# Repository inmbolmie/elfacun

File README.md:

# Elfacun Chess Interface Module

## News

__(2026/02/07): Elfacun software version R17 released with new Chessconnect mode :__ Link: ----- __[R17 files](https://github.com/inmbolmie/elfacun/releases/tag/R17)__ ----- Installation instructions: ----- __[Update Elfacun](./MANUAL.md#update-elfacun-software)__

## Elfacun chess module

This is an ongoing hardware project to create a chess module compatible with the old Mephisto modular boards (Exclusive, Modular, München) that will provide connectivity to a wide variety of chess apps and services.

The project currently comprises three devices:

* Elfacun chess module, that is the main module that enables the connectivity of modern apps to the Mephisto chess boards
* Brocoli power module, to be able to power Elfacun, the Mephisto board and some original modules from a regular USB power bank to get a true wireless chess board.
* Diablillo bridge adapter, that allows to connect wirelessly a physical Millennium chess module to Elfacun.

The hardware as well as software developed for it are published here under the GPL license.

To assist in the release of the module, I provide here links to some basic documentation:

* [V1 and V2 modules description and features](./DESCRIPTION.md)
* [Brocoli power module](./BROCOLI.md)
* [Diablillo bridge adapter](./DIABLILLO.md)
* [Compatibility chart](./COMPATIBILITY.md)
* [Limitations and remarks](./LIMITATIONS.md)
* [Operation manual](./MANUAL.md)
* [Make your own module](./SOURCE.md)

## Old News

__(2025/06/15): Source code and design files for V2 module released: ----- [Make your own module](./SOURCE.md)__

__(2025/02/23): Elfacun software version R15 released with chess 960 support:__ Link: ----- __[R15 files](https://github.com/inmbolmie/elfacun/releases/tag/R15)__ ----- Installation instructions: ----- __[Update Elfacun](./MANUAL.md#update-elfacun-software)__

__(2025/02/23): Diablillo software version R15 released with bug fixes:__ Link: ----- __[R15 files](https://github.com/inmbolmie/elfacun/releases/tag/R15)__ ----- Installation instructions: ----- __[Update Diabillo](./DIABLILLO.md#update-diablillo-software)__

__(2024/05/26): Elfacun software version R14 released with bug fixes:__ Link: ----- __[R14 files](https://github.com/inmbolmie/elfacun/releases/tag/R14)__ ----- Installation instructions: ----- __[Update Elfacun](./MANUAL.md#update-elfacun-software)__

__(2024/01/19): Elfacun software version R12 released with improvements for Lichess mode:__ Link: ----- __[R12 files](https://github.com/inmbolmie/elfacun/releases/tag/R12)__ ----- Installation instructions: ----- __[Update Elfacun](./MANUAL.md#update-elfacun-software)__

__(2023/09/16): Elfacun software version R11 released with new Chessnut-compatible mode:__ Link: ----- __[R11 files](https://github.com/inmbolmie/elfacun/releases/tag/R11)__ ----- Installation instructions: ----- __[Update Elfacun](./MANUAL.md#update-elfacun-software)__

__(2023/07/13): Elfacun software version R10 released with bug fixes:__ Link: ----- __[R10 files](https://github.com/inmbolmie/elfacun/releases/tag/R10)__ ----- Installation instructions: ----- __[Update Elfacun](./MANUAL.md#update-elfacun-software)__

__(2023/06/12): Elfacun software version R9 released with bug fixes:__ Link: ----- __[R9 files](https://github.com/inmbolmie/elfacun/releases/tag/R9)__ ----- Installation instructions: ----- __[Update Elfacun](./MANUAL.md#update-elfacun-software)__

__(2023/06/07): Elfacun software version R8 released with support for the new _Diablillo_ device:__ Link: ----- __[R8 files](https://github.com/inmbolmie/elfacun/releases/tag/R8)__ ----- Installation instructions: ----- __[Update Elfacun](./MANUAL.md#update-elfacun-software)__

__(2023/03/05): Elfacun software version R7 released with on-screen LED indications in passive mode, board position storage and customizable sound and BLE power level:__ Link: ----- __[R7 files](https://github.com/inmbolmie/elfacun/releases/tag/R7)__ ----- Installation instructions: ----- __[Update Elfacun](./MANUAL.md#update-elfacun-software)__

__(2023/02/08): Elfacun software version R6 released with opponent ELO range on Lichess challenges:__ Link: ----- __[R6 files](https://github.com/inmbolmie/elfacun/releases/tag/R6)__ ----- Installation instructions: ----- __[Update Elfacun](./MANUAL.md#update-elfacun-software)__

__(2023/01/30): Elfacun software version R5 released with some bug fixes:__ Link: ----- __[R5 files](https://github.com/inmbolmie/elfacun/releases/tag/R5)__ ----- Installation instructions: ----- __[Update Elfacun](./MANUAL.md#update-elfacun-software)__

__(2023/01/28): Elfacun hardware version 2 released with new features and improved compatibility with original modules:__ Links: ----- __[V2 features](./DESCRIPTION.md#features)__ ----- __[V2 manual](./MANUAL.md#new-v1-and-v2-features)__ ----- __[V2 compatibility](./COMPATIBILITY.md#v2-with-original-mephisto-modules)__

__(2023/01/28): Brocoli battery power module for Elfacun:__ Link: ----- __[Brocoli power module](./BROCOLI.md)__

__(2022/05/04): Elfacun software version R4 released with some bug fixes: [R4 files](https://github.com/inmbolmie/elfacun/releases/tag/R4)__ Installation instructions: ----- __[Update Elfacun](./MANUAL.md#update-elfacun-software)__

__(2022/09/03): Source code and design files released: ----- [Make your own module](./SOURCE.md)__

_"DGT", "Millennium", "Mephisto", "Chessnut" and "IChessOne" are trademarks of their respective owners.
All the trademarks are used nominatively to indicate compatibility, and do not indicate affiliation to or endorsement by the trademark owners._

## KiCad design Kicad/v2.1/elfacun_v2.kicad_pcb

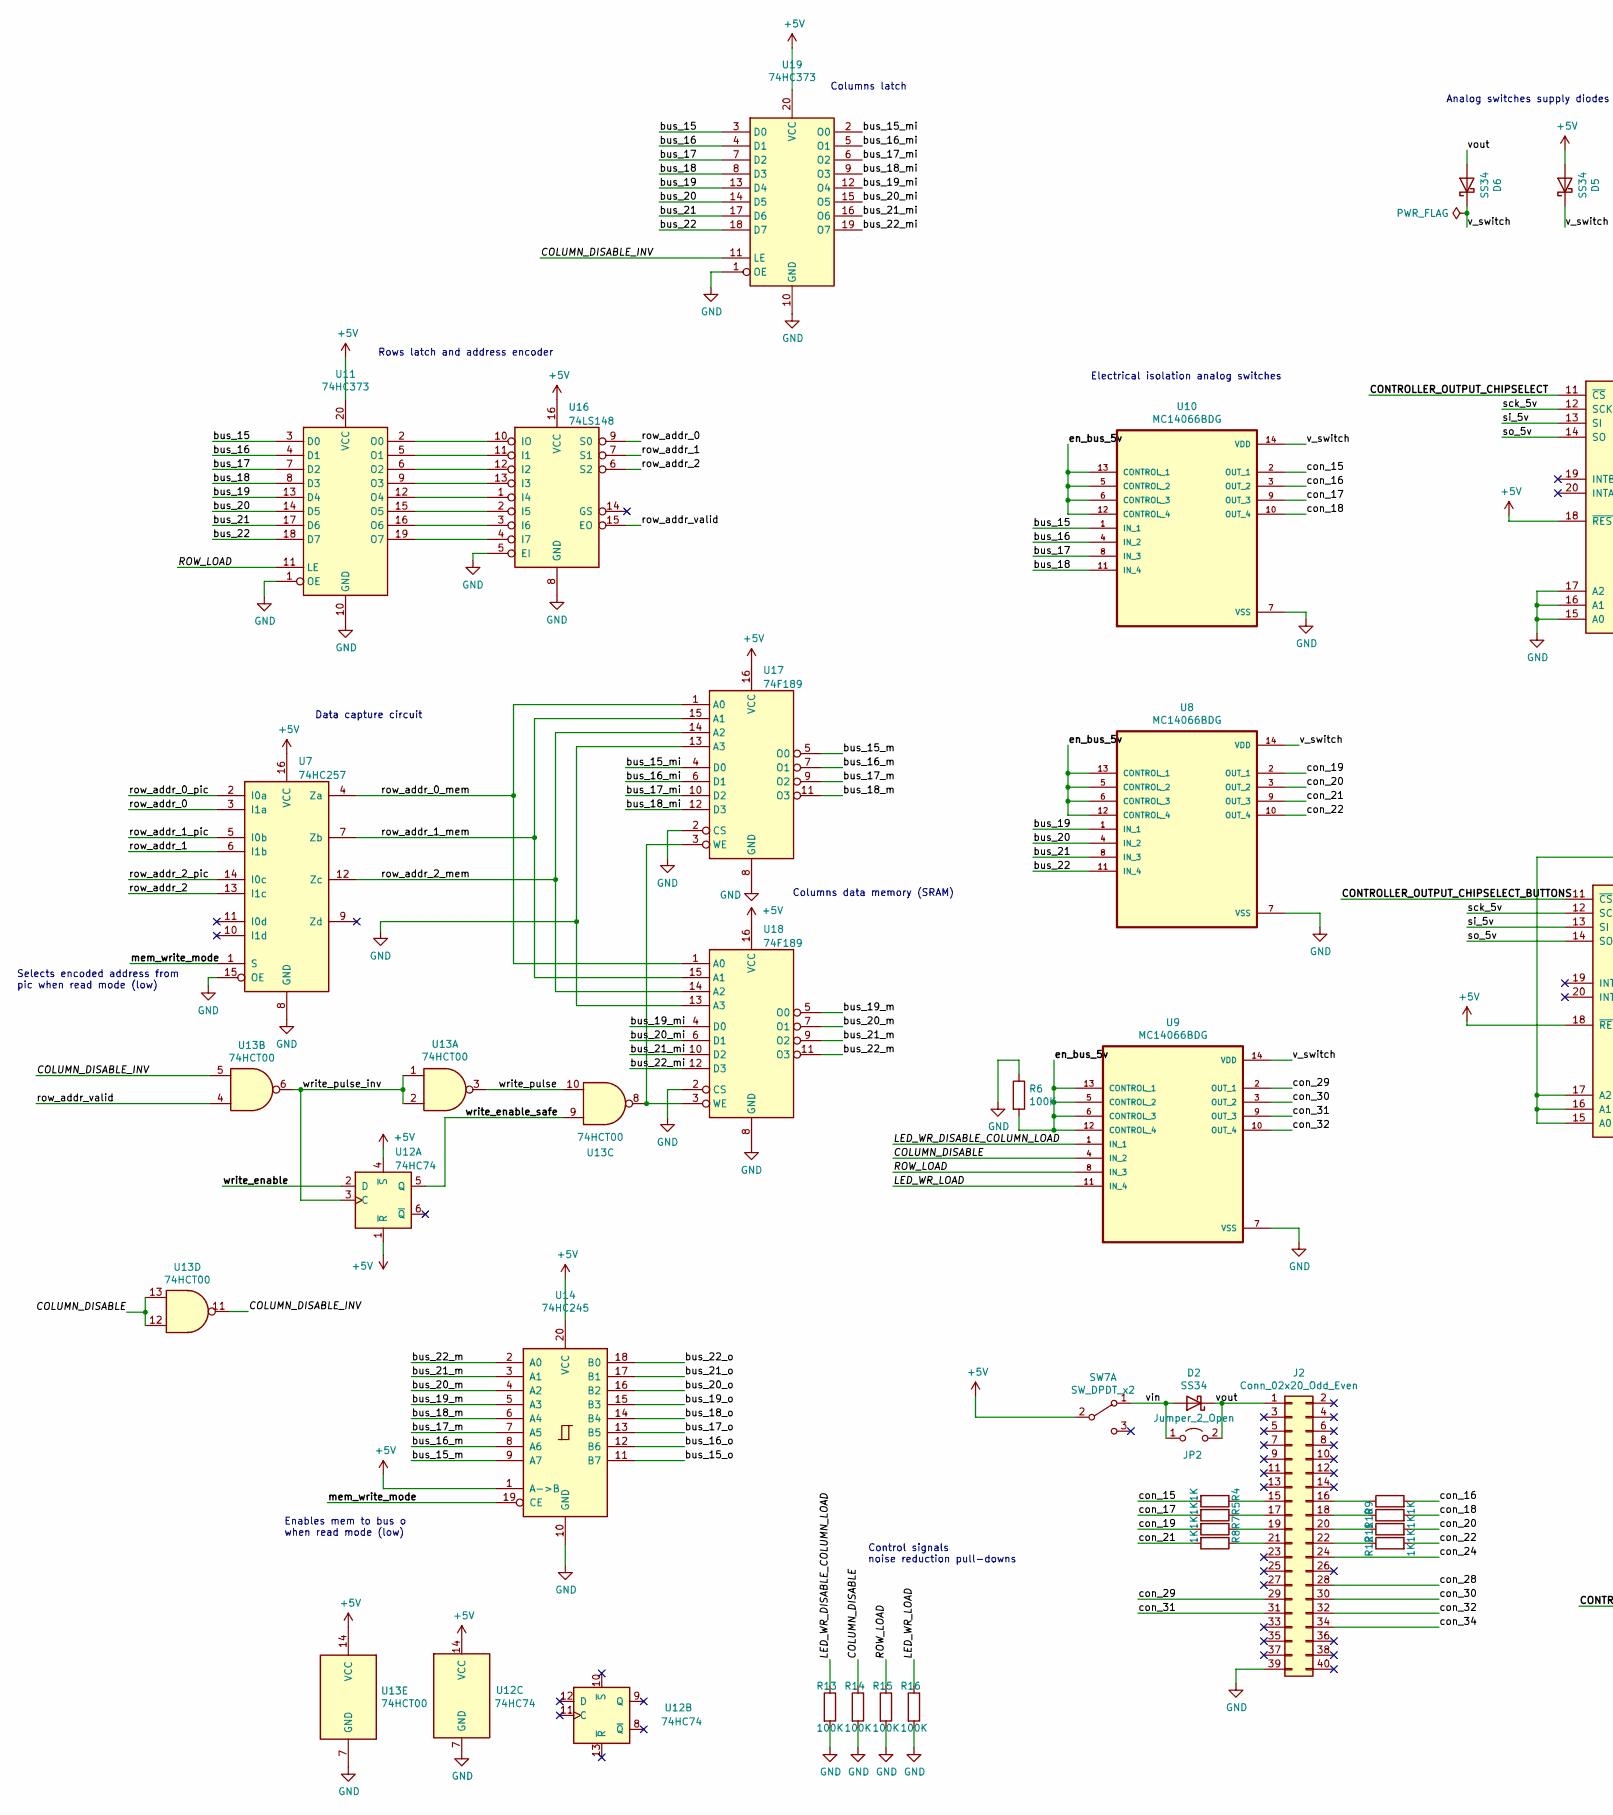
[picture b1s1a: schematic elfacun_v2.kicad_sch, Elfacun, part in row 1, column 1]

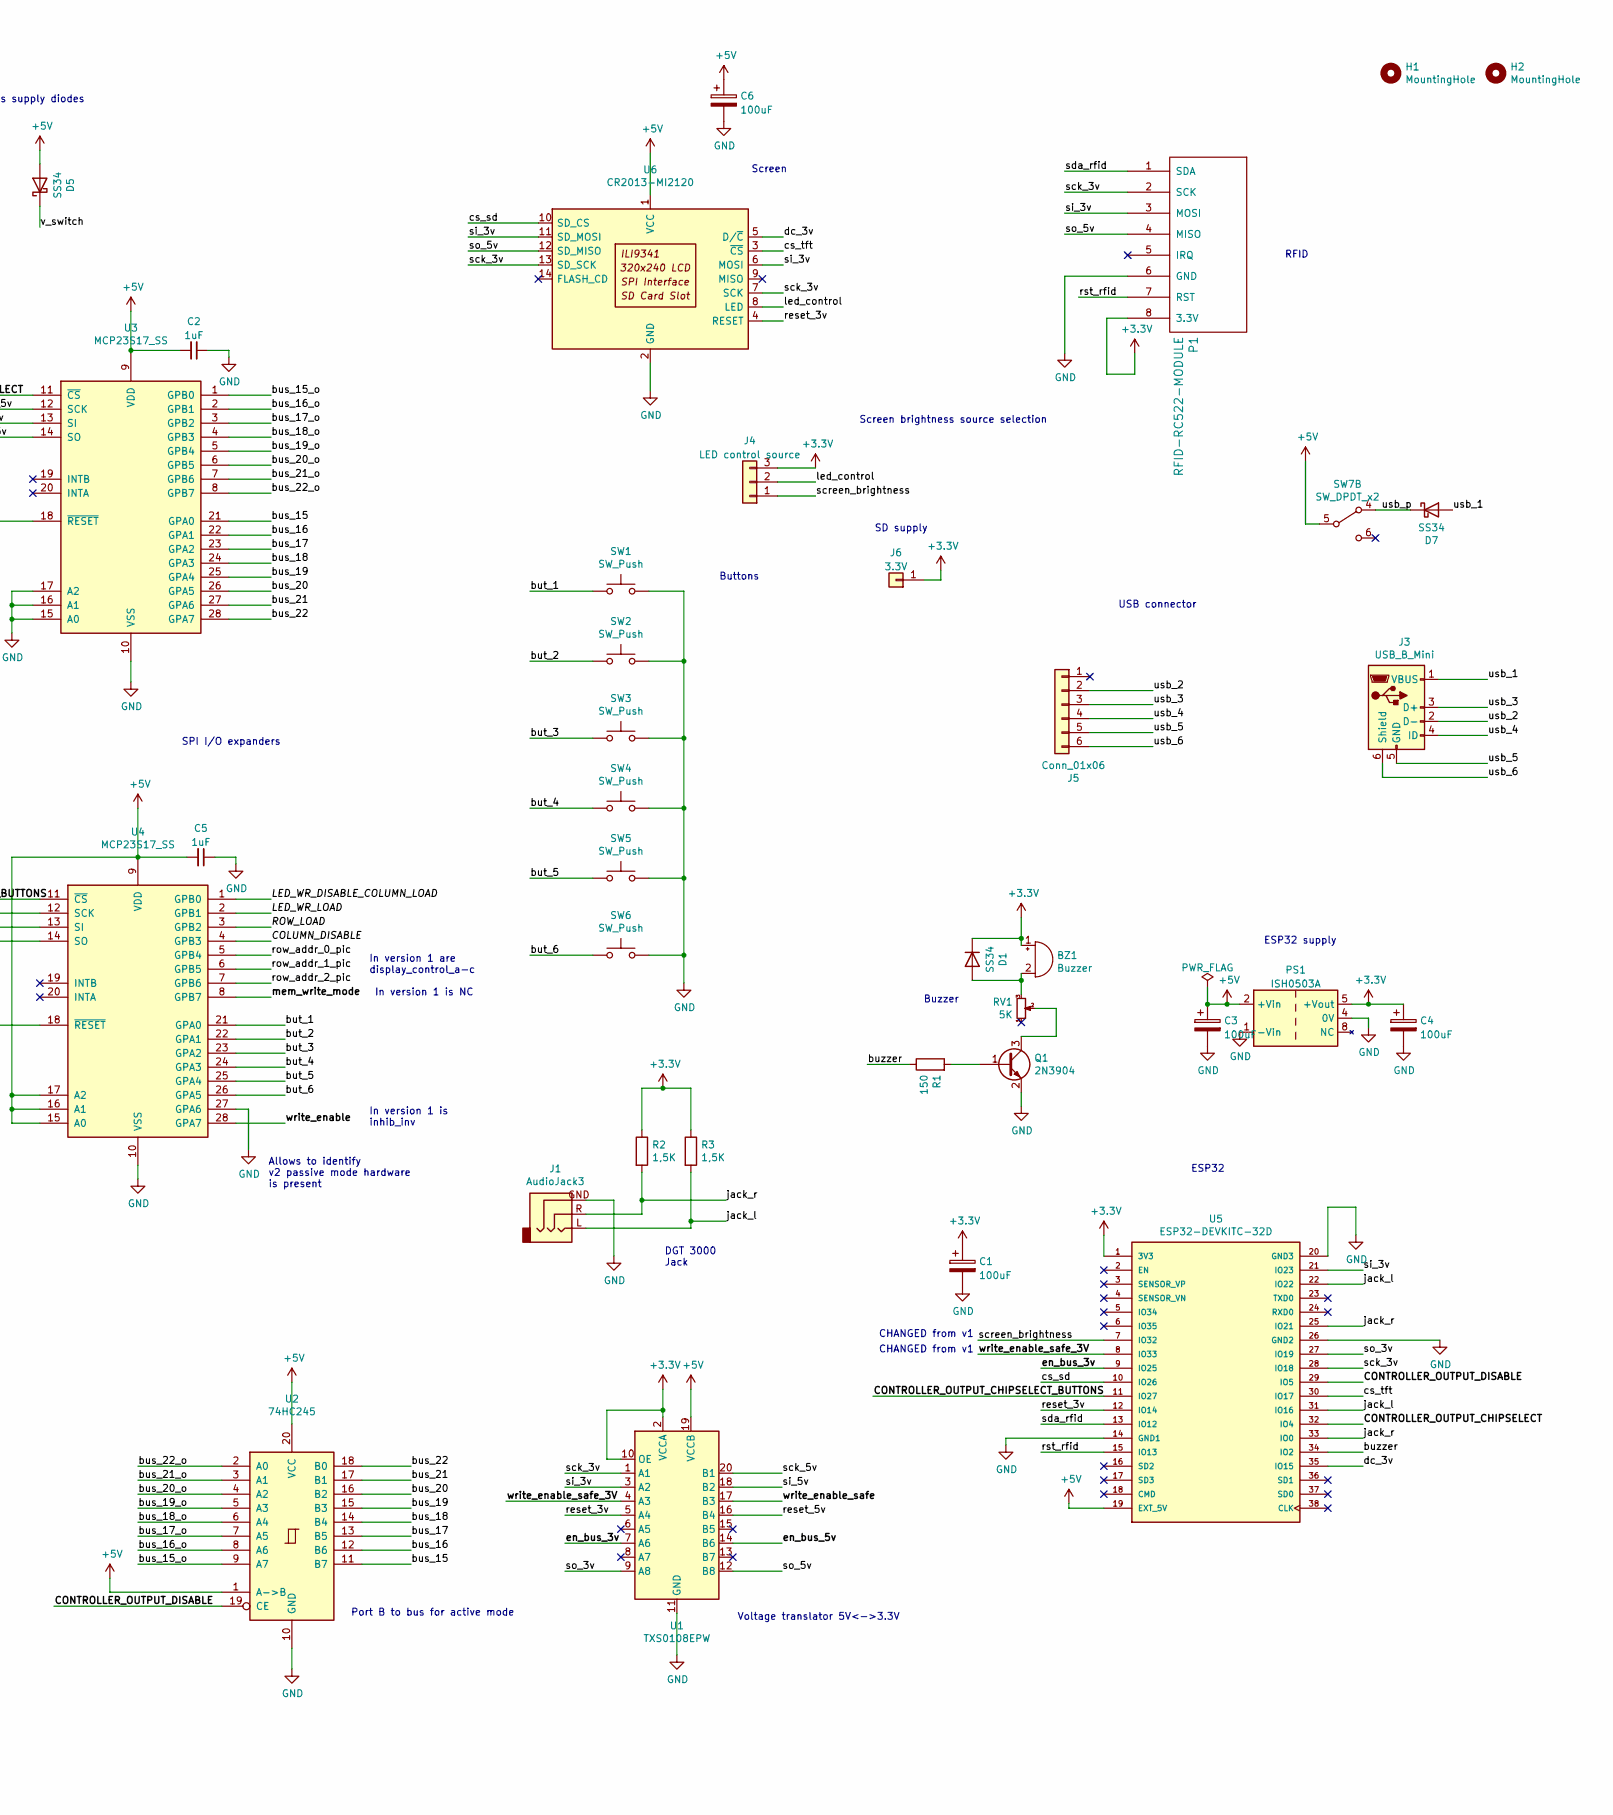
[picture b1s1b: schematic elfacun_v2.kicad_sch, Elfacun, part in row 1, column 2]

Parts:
BZ1: Buzzer; MagneticBuzzer_ProSignal_ABT-410-RC
C1, C3, C4, C6: 100uF; C_1206_3216Metric; LCSC C15008
C2, C5: 1uF; C_0603_1608Metric; LCSC C15849
D1, D2, D5, D6, D7: SS34; D_SMA; LCSC C8678
H1, H2: MountingHole; MountingHole_3.5mm
J1: AudioJack3; AUDIO-TH_PJ-3059-X; LCSC C319114
J2: Conn_02x20_Odd_Even; PinHeader_2x20_P2.54mm_Horizontal
J3: USB_B_Mini; USB_Mini-B_Tensility_54-00023_Vertical; LCSC C13453
J4: LED control source; PinHeader_1x03_P2.54mm_Vertical
J5: Conn_01x06; PinHeader_1x06_P2.54mm_Horizontal
J6: 3.3V; PinHeader_1x01_P2.54mm_Horizontal
JP2: Jumper_2_Open; PinHeader_1x02_P2.54mm_Vertical
P1: RFID-RC522-MODULE; PinHeader_1x08_P2.54mm_Vertical
PS1: ISH0503A; ISE0303A
Q1: 2N3904; SOT-23; LCSC C18536
R1: 150; R_0603_1608Metric; LCSC C22808
R2, R3: 1,5K; R_0603_1608Metric; LCSC C22843
R4, R5, R7, R8, R9, R10, R11, R12: 1K; R_0603_1608Metric; LCSC C21190
R6, R13, R14, R15, R16: 100K; R_0603_1608Metric; LCSC C25803
RV1: 5K; RES-ADJ-SMD_G32AT; LCSC C128119
SW1, SW2, SW3, SW4, SW5, SW6: SW_Push; honyone_pb13_switch
SW7: SW_DPDT_x2; SW-TH_K3-2235S-K1
U1: TXS0108EPW; TSSOP-20_4.4x6.5mm_P0.65mm; LCSC C53406
U2, U14: 74HC245; SO-20_5.3x12.6mm_P1.27mm; LCSC C133641
U3, U4: MCP23S17_SS; DIP-28_W7.62mm; LCSC C145413
U5: ESP32-DEVKITC-32D; MODULE_ESP32-DEVKITC-32D
U6: CR2013-MI2120
U7: 74HC257; SOIC-16_3.9x9.9mm_P1.27mm; LCSC C7645
U8, U9, U10: MC14066BDG; SOIC-14_3.9x8.7mm_P1.27mm; LCSC C52828
U11, U19: 74HC373; TSSOP-20_4.4x6.5mm_P0.65mm; LCSC C132998
U12: 74HC74; SO-14_3.9x8.65mm_P1.27mm; LCSC C39990
U13: 74HCT00; SOIC-14_3.9x8.7mm_P1.27mm
U16: 74LS148; SOP-16_3.9x9.9mm_P1.27mm; LCSC C521196
U17, U18: 74F189; DIP-16_W7.62mm

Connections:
+3V3: BZ1.1 (-), C1.1, C4.1, D1.1 (K), J4.3, J6.1, P1.8 (3.3V), PS1.5 (+Vout), R2.1, R3.1, U1.2 (VCCA), U1.10 (OE), U5.1 (3V3)
+5V: C2.2, C3.1, C5.2, C6.1, D5.2 (A), PS1.2 (+Vin), SW7.2 (B), SW7.5 (B), U1.19 (VCCB), U2.1 (A->B), U2.20 (VCC), U3.9 (VDD), U3.18 (~RESET), U4.9 (VDD), U4.15 (A0), U4.16 (A1), U4.17 (A2), U4.18 (~RESET), U5.19 (EXT_5V), U6.1 (VCC), U7.16 (VCC), U11.20 (VCC), U12.1 (~R), U12.4 (~S), U12.14 (VCC), U13.14 (VCC), U14.1 (A->B), U14.20 (VCC), U16.16 (VCC), U17.16 (VCC), U18.16 (VCC), U19.20 (VCC)
/COLUMN_DISABLE: R14.1, U4.4 (GPB3), U9.4 (IN_2), U13.12, U13.13
/COLUMN_DISABLE_INV: U13.5, U13.11, U19.11 (LE)
/CONTROLLER_OUTPUT_CHIPSELECT: U3.11 (~CS), U5.32 (IO4)
/CONTROLLER_OUTPUT_CHIPSELECT_BUTTONS: U4.11 (~CS), U5.11 (IO27)
/CONTROLLER_OUTPUT_DISABLE: U2.19 (CE), U5.29 (IO5)
/LED_WR_DISABLE_COLUMN_LOAD: R13.1, U4.1 (GPB0), U9.1 (IN_1)
/LED_WR_LOAD: R16.1, U4.2 (GPB1), U9.11 (IN_4)
/ROW_LOAD: R15.1, U4.3 (GPB2), U9.8 (IN_3), U11.11 (LE)
/bus_15: U2.11 (B7), U3.21 (GPA0), U10.1 (IN_1), U11.3 (D0), U19.3 (D0)
/bus_15_m: U14.9 (A7), U17.5 (O0)
/bus_15_mi: U17.4 (D0), U19.2 (O0)
/bus_15_o: U2.9 (A7), U3.1 (GPB0), U14.11 (B7)
/bus_16: U2.12 (B6), U3.22 (GPA1), U10.4 (IN_2), U11.4 (D1), U19.4 (D1)
/bus_16_m: U14.8 (A6), U17.7 (O1)
/bus_16_mi: U17.6 (D1), U19.5 (O1)
/bus_16_o: U2.8 (A6), U3.2 (GPB1), U14.12 (B6)
/bus_17: U2.13 (B5), U3.23 (GPA2), U10.8 (IN_3), U11.7 (D2), U19.7 (D2)
/bus_17_m: U14.7 (A5), U17.9 (O2)
/bus_17_mi: U17.10 (D2), U19.6 (O2)
/bus_17_o: U2.7 (A5), U3.3 (GPB2), U14.13 (B5)
/bus_18: U2.14 (B4), U3.24 (GPA3), U10.11 (IN_4), U11.8 (D3), U19.8 (D3)
/bus_18_m: U14.6 (A4), U17.11 (O3)
/bus_18_mi: U17.12 (D3), U19.9 (O3)
/bus_18_o: U2.6 (A4), U3.4 (GPB3), U14.14 (B4)
/bus_19: U2.15 (B3), U3.25 (GPA4), U8.1 (IN_1), U11.13 (D4), U19.13 (D4)
/bus_19_m: U14.5 (A3), U18.5 (O0)
/bus_19_mi: U18.4 (D0), U19.12 (O4)
/bus_19_o: U2.5 (A3), U3.5 (GPB4), U14.15 (B3)
/bus_20: U2.16 (B2), U3.26 (GPA5), U8.4 (IN_2), U11.14 (D5), U19.14 (D5)
/bus_20_m: U14.4 (A2), U18.7 (O1)
/bus_20_mi: U18.6 (D1), U19.15 (O5)
/bus_20_o: U2.4 (A2), U3.6 (GPB5), U14.16 (B2)
/bus_21: U2.17 (B1), U3.27 (GPA6), U8.8 (IN_3), U11.17 (D6), U19.17 (D6)
/bus_21_m: U14.3 (A1), U18.9 (O2)
/bus_21_mi: U18.10 (D2), U19.16 (O6)
/bus_21_o: U2.3 (A1), U3.7 (GPB6), U14.17 (B1)
/bus_22: U2.18 (B0), U3.28 (GPA7), U8.11 (IN_4), U11.18 (D7), U19.18 (D7)
/bus_22_m: U14.2 (A0), U18.11 (O3)
/bus_22_mi: U18.12 (D3), U19.19 (O7)
/bus_22_o: U2.2 (A0), U3.8 (GPB7), U14.18 (B0)
/but_1: SW1.1, U4.21 (GPA0)
/but_2: SW2.1, U4.22 (GPA1)
/but_3: SW3.1, U4.23 (GPA2)
/but_4: SW4.1, U4.24 (GPA3)
/but_5: SW5.1, U4.25 (GPA4)
/but_6: SW6.1, U4.26 (GPA5)
/buzzer: R1.1, U5.34 (IO2)
/con_15: R4.2, U10.2 (OUT_1)
/con_16: R9.2, U10.3 (OUT_2)
/con_17: R5.2, U10.9 (OUT_3)
/con_18: R10.2, U10.10 (OUT_4)
/con_19: R7.2, U8.2 (OUT_1)
/con_20: R11.2, U8.3 (OUT_2)
/con_21: R8.2, U8.9 (OUT_3)
/con_22: R12.2, U8.10 (OUT_4)
/con_24: J2.24
/con_28: J2.28
/con_29: J2.29, U9.2 (OUT_1)
/con_30: J2.30, U9.3 (OUT_2)
/con_31: J2.31, U9.9 (OUT_3)
/con_32: J2.32, U9.10 (OUT_4)
/con_34: J2.34
/cs_sd: U5.10 (IO26), U6.10 (SD_CS)
/cs_tft: U5.30 (IO17), U6.3 (~CS)
/dc_3v: U5.35 (IO15), U6.5 (D/~C)
/en_bus_3v: U1.7 (A6), U5.9 (IO25)
/en_bus_5v: R6.2, U1.14 (B6), U8.5 (CONTROL_2), U8.6 (CONTROL_3), U8.12 (CONTROL_4), U8.13 (CONTROL_1), U9.5 (CONTROL_2), U9.6 (CONTROL_3), U9.12 (CONTROL_4), U9.13 (CONTROL_1), U10.5 (CONTROL_2), U10.6 (CONTROL_3), U10.12 (CONTROL_4), U10.13 (CONTROL_1)
/jack_l: J1.L, R3.2, U5.22 (IO22), U5.31 (IO16)
/jack_r: J1.R, R2.2, U5.25 (IO21), U5.33 (IO0)
/led_control: J4.2, U6.8 (LED)
/mem_write_mode: U4.8 (GPB7), U7.1 (S), U14.19 (CE)
/reset_3v: U1.5 (A4), U5.12 (IO14), U6.4 (RESET)
/reset_5v: U1.16 (B4)
/row_addr_0: U7.3 (I1a), U16.9 (S0)
/row_addr_0_mem: U7.4 (Za), U17.1 (A0), U18.1 (A0)
/row_addr_0_pic: U4.5 (GPB4), U7.2 (I0a)
/row_addr_1: U7.6 (I1b), U16.7 (S1)
/row_addr_1_mem: U7.7 (Zb), U17.15 (A1), U18.15 (A1)
/row_addr_1_pic: U4.6 (GPB5), U7.5 (I0b)
/row_addr_2: U7.13 (I1c), U16.6 (S2)
/row_addr_2_mem: U7.12 (Zc), U17.14 (A2), U18.14 (A2)
/row_addr_2_pic: U4.7 (GPB6), U7.14 (I0c)
/row_addr_valid: U13.4, U16.15 (EO)
/rst_rfid: P1.7 (RST), U5.15 (IO13)
/sck_3v: P1.2 (SCK), U1.1 (A1), U5.28 (IO18), U6.7 (SCK), U6.13 (SD_SCK)
/sck_5v: U1.20 (B1), U3.12 (SCK), U4.12 (SCK)
/screen_brightness: J4.1, U5.7 (IO32)
/sda_rfid: P1.1 (SDA), U5.13 (IO12)
/si_3v: P1.3 (MOSI), U1.3 (A2), U5.21 (IO23), U6.6 (MOSI), U6.11 (SD_MOSI)
/si_5v: U1.18 (B2), U3.13 (SI), U4.13 (SI)
/so_3v: U1.9 (A8), U5.27 (IO19)
/so_5v: P1.4 (MISO), U1.12 (B8), U3.14 (SO), U4.14 (SO), U6.12 (SD_MISO)
/usb_1: D7.2 (A), J3.1 (VBUS)
/usb_2: J3.2 (D-), J5.2
/usb_3: J3.3 (D+), J5.3
/usb_4: J3.4 (ID), J5.4
/usb_5: J3.5 (GND), J5.5
/usb_6: J3.6 (Shield), J5.6
/usb_p: D7.1 (K), SW7.4 (A)
/v_switch: D5.1 (K), D6.1 (K), U8.14 (VDD), U9.14 (VDD), U10.14 (VDD)
/vin: D2.2 (A), JP2.1 (A), SW7.1 (A)
/vout: D2.1 (K), D6.2 (A), J2.1, JP2.2 (B)
/write_enable: U4.28 (GPA7), U12.2 (D)
/write_enable_safe: U1.17 (B3), U12.5 (Q), U13.9
/write_enable_safe_3V: U1.4 (A3), U5.8 (IO33)
/write_pulse: U13.3, U13.10
/write_pulse_inv: U12.3 (C), U13.1, U13.2, U13.6
GND: C1.2, C2.1, C3.2, C4.2, C5.1, C6.2, J1.GND, J2.39, P1.6 (GND), PS1.1 (-Vin), PS1.4 (0V), Q1.2 (E), R6.1, R13.2, R14.2, R15.2, R16.2, SW1.2, SW2.2, SW3.2, SW4.2, SW5.2, SW6.2, U1.11 (GND), U2.10 (GND), U3.10 (VSS), U3.15 (A0), U3.16 (A1), U3.17 (A2), U4.10 (VSS), U4.27 (GPA6), U5.14 (GND1), U5.20 (GND3), U5.26 (GND2), U6.2 (GND), U7.8 (GND), U7.15 (OE), U8.7 (VSS), U9.7 (VSS), U10.7 (VSS), U11.1 (OE), U11.10 (GND), U12.7 (GND), U13.7 (GND), U14.10 (GND), U16.5 (EI), U16.8 (GND), U17.2 (CS), U17.8 (GND), U17.13 (A3), U18.2 (CS), U18.8 (GND), U18.13 (A3), U19.1 (OE), U19.10 (GND)
unnamed: BZ1.2 (+), D1.2 (A), RV1.3
unnamed: J2.15, R4.1
unnamed: J2.16, R9.1
unnamed: J2.17, R5.1
unnamed: J2.18, R10.1
unnamed: J2.19, R7.1
unnamed: J2.20, R11.1
unnamed: J2.21, R8.1
unnamed: J2.22, R12.1
unnamed: Q1.1 (B), R1.2
unnamed: Q1.3 (C), RV1.2
unnamed: U11.2 (O0), U16.10 (IO)
unnamed: U11.5 (O1), U16.11 (I1)
unnamed: U11.6 (O2), U16.12 (I2)
unnamed: U11.9 (O3), U16.13 (I3)
unnamed: U11.12 (O4), U16.1 (I4)
unnamed: U11.15 (O5), U16.2 (I5)
unnamed: U11.16 (O6), U16.3 (I6)
unnamed: U11.19 (O7), U16.4 (I7)
unnamed: U13.8, U17.3 (WE), U18.3 (WE)

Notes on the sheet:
Buzzer
Enables mem to bus o when read mode (low)
Selects encoded address from pic when read mode (low)
ESP32
Analog switches supply diodes
Screen brightness source selection
Port B to bus for active mode
Columns data memory (SRAM)
SD supply
USB connector
Buttons
CHANGED from v1
SPI I/O expanders
DGT 3000 Jack
RFID
Screen
In version 1 is NC
ESP32 supply
Rows latch and address encoder
Control signals noise reduction pull-downs
Electrical isolation analog switches
Data capture circuit
In version 1 is inhib_inv
Allows to identify v2 passive mode hardware is present
In version 1 are display_control_a-c
Voltage translator 5V<->3.3V
Columns latch

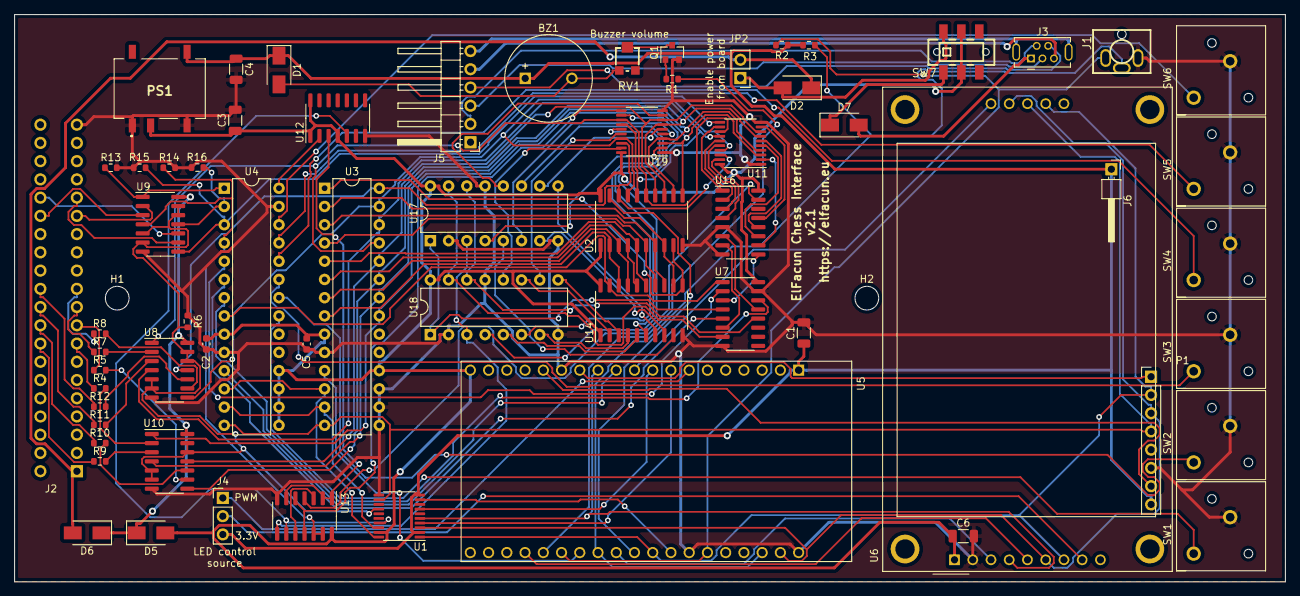
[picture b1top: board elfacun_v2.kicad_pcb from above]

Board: 2 copper layers, 177.0 x 79.0 mm, 66 parts (0 on the bottom side), 126 nets.

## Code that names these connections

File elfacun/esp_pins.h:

/*  
    ElFacun Chess Module software for ESP32
    © 2022 Inmbolmie inmbolmie [at] gmail [dot] com
    Distributed under the GNU GPL V3.0 license
    
    This program is distributed WITHOUT ANY WARRANTY, even the 
    implied warranty of MERCHANTABILITY or FITNESS FOR A PARTICULAR 
    PURPOSE.  See the GNU General Public License for more details.
*/

//ESP32 I/O PORTS ASSIGNMENTS
//00 Audio Jack R (I2C master)

//02 Buzzer
//04 CONTROLLER OUTPUT CS
//05 CONTROLLER OUTPUT DISABLE

//12 RFID CS
//13 RFID RESET
//14 SPI RESET 3V
//15 DISPLAY D/C 3V
//16 Audio Jack L (I2C master)
//17 DISPLAY CS
//18 SPI SCK 3V
//19 SPI SO 3V

//21 Audio Jack R (I2C slave)
//22 Audio Jack L (I2C slave)
//23 SPI SI 3V

//25 ENABLE BUS SWITCHES
//26 SD CARD CS
//27 CONTROLLER OUTPUT BUTTONS CS

//32 LATCH DISABLE B (columns)
//33 LATCH DISABLE A (rows)


//Board interface control pins

//RFID
#define RFID_CS 12

//SD INTERFACE
#define SD_CS 26

//ENABLE BUS SWITCHES
#define EN_BUS 25

//Data from controller to board
#define CONTROLLER_OUTPUT_DISABLE 5
#define CONTROLLER_OUTPUT_CHIPSELECT 4
#define CONTROLLER_OUTPUT_CHIPSELECT_BUTTONS 27


//Board latches controlled through 40-pin connector with the 23S17. So the numbers are 23S17 port numbers
//BUS_29
#define LED_WR_DISABLE_COLUMN_LOAD_EX 8
//BUS_32
#define LED_WR_LOAD_EX 9
//BUS_31
#define ROW_LOAD_EX 10
//BUS_30
#define COLUMN_DISABLE_EX 11
//DISPLAY CONTROL
#define DISPLAY_CTRL_A 12
#define DISPLAY_CTRL_B 13
#define DISPLAY_CTRL_C 14

//Special data latches for passive mode
#define LATCH_ROWS_DISABLE 33
#define LATCH_COLUMNS_DISABLE 32

//probe to get passive latch inhibition state
#define INHIB_INV 7

//Buzzer pin
#define BUZZER 2


//ELFACUN2 SPECIFIC PINS

#define HARDWARE_V2_DETECT 6
#define MEM_WRITE_ENABLE 7  // on V1 is INHIB_INV
#define MEM_ADDR_0 12 // on V1 is DISPLAY_CTRL_A 0
#define MEM_ADDR_1 13 // on V1 is DISPLAY_CTRL_B 1
#define MEM_ADDR_2 14 // on V1 is DISPLAY_CTRL_C 2
#define MEM_ADDR_SRC 15 // on V1 is NC

#define WRITE_ENABLE_SAFE 33 // on V1 is LATCH_ROWS_DISABLE

#define MEM_ADDR_SRC_BUS true
#define MEM_ADDR_SRC_PIC false

#define SCREEN_BRIGHTNESS 32 // on V1 is LATCH_COLUMNS_DISABLE
 

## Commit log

2021-11-05 Create CNAME
2022-02-22 Initial doc commit
2022-02-23 BLE now working with Grahan O'Neill drivers
2022-02-25 Specify DGT-3000 orientation at module startup
2022-02-27 Indicate that the screen size is 2.2''
2022-03-05 Powering the module section
2022-03-09 Pictures
2022-04-10 Update MANUAL.md
    USB driver install link
2022-05-04 New update instructions
2022-05-04 R4 announcement
2022-05-05 RFID tag specification
2022-07-12 New module and board compatibility reports
2022-09-03 Source code and design files for v1.1 module
2023-01-26 Updated documentation for Elfacun module version 2 and Brocoli power module
2023-01-28 Chess.com Android app is not fully functional
2023-01-30 Link to release R5
2023-02-11 R6 release with opponent ELO ranges on Lichess
2023-03-06 R7 new features
2023-06-12 New R9 release
2023-06-14 Driver attribution
2023-07-13 Compatibility update
2023-09-16 New mode C
2024-01-19 R12 changes
2024-01-19 Chessnut app compatibility
2024-05-26 R14 fixes
2025-02-23 Diablillo documentation and R15 features
2025-02-23 Link to R15
2025-02-23 Fix readme
2025-06-15 V2 firmware
2025-06-15 V2 hardware
2025-11-09 Fix first row led flicker
2026-02-07 Chessconnect mode

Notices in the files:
Kicad/v2.1/elfacun_v2.kicad_sch:
Distributed under GPL3 license
